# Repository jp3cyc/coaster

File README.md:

# coaster
光る！コースタです。いざって時(e.g. 友達が遊びに来た、地震、台風の時とか)にはArduinoとしても活躍します。

# 用意するもの
## 部品
- チップLED 1608サイズ 12個
- チップ抵抗 270Ω 1608サイズ 12個
- チップ抵抗 10kΩ 1608サイズ 1個
- ATMEGA328P-AU 1個
- 基板実装型スイッチ 1個
- CR2032表面実装型ケース 1個
- CR2032 1個

## 道具
- AVR書き込み機　または Arduino UNO
- はんだごて
- はんだ
- リフロー炉（あれば楽）
- クリームはんだ（あれば楽）
- ピンセット（あれば便利）
- 顕微鏡（あれば便利）
- レーザ加工機（自宅にあると◎、ない場合はファボラボ or カインズに行く、カッターで頑張るのもあり）

# How to makke
1. プリント基板を注文する。Fusion PCB、PCBgogo、Elecrowとか。10枚$10＋送料です。coaster/circuit/garb/coaster-garbdata.zipを送るだけ
1. プリント基板が届くまでに部品を注文する。http://aki.prioris.jp/list/31d5aa3b-d171-41f0-a121-0a985a356ac1/ ワンクリックですべての部品があきづきカートに入ります。一個分の部品です。
1. コースタ基板を入れるためのケースを作ります。coaster-cutting.aiに入っているデータを誤自宅のレーザカッタで切断します。データはIllustrator形式ですが、みるだけならCoral Drawとかでもいけます。
1. はんだづけします。
1. AVRのFuseビットを変更します。lfuse:0xe2, hfuse:0xde, efuse:0x07（書き込めない場合はY1に8MHzの水晶、C1,C2に22pFのコンデンサをつけてみる）(firwareフォルダにコマンドが入っています）
1. プログラムを書き込みます。coaster-firmware/coaster-firmware.ino.with_bootloader.eightanaloginputs.hexを書き込みます。
1. ボタン電池を入れて、スイッチを入れるとつくはずです。つかなければ、電池残量、スイッチ、はんだ付けを見てみます。

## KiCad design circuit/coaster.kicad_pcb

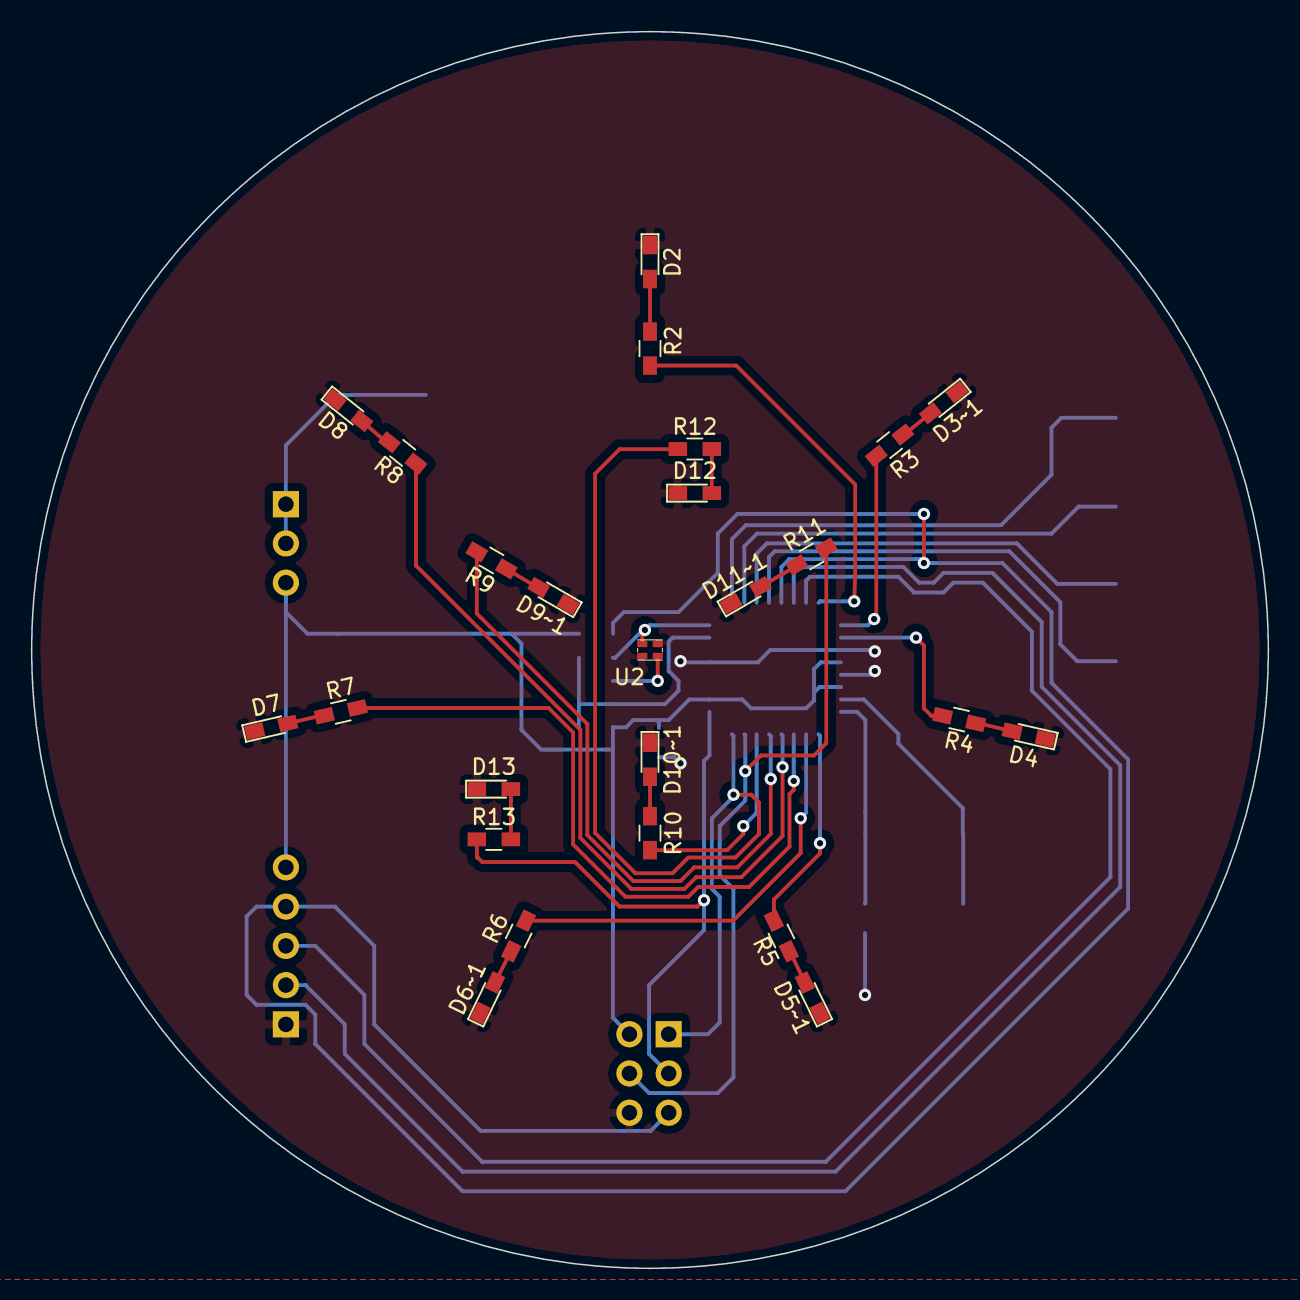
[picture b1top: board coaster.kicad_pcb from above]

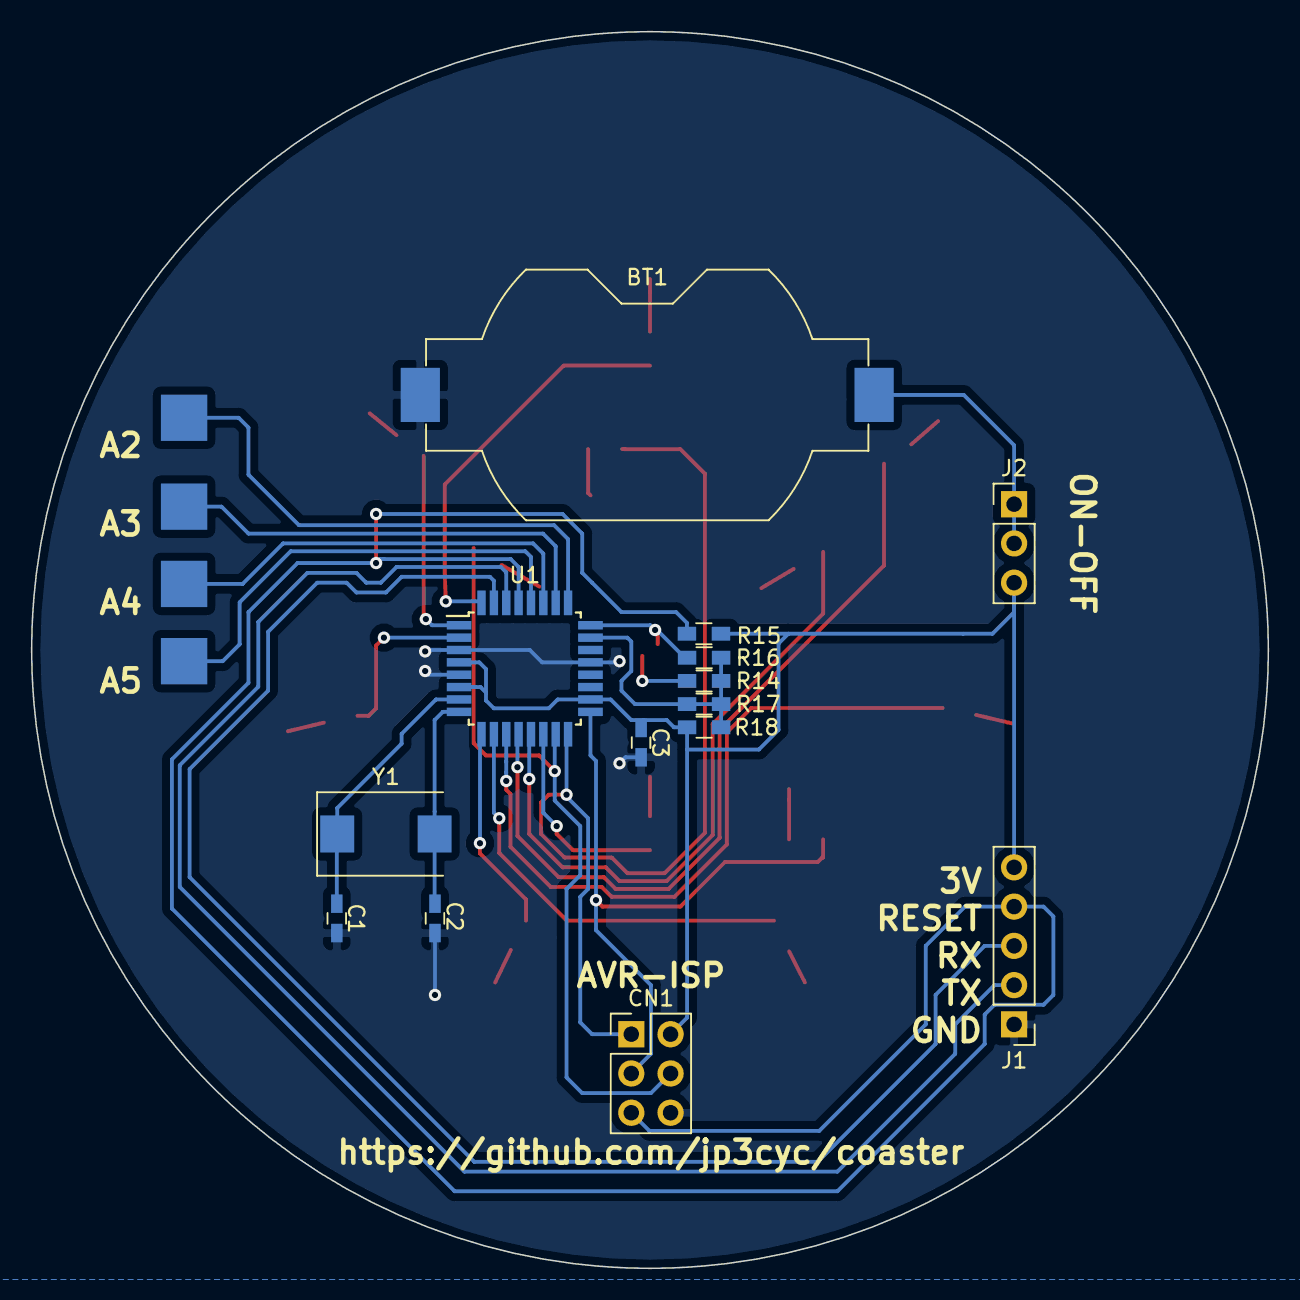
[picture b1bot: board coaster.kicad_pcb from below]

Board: 2 copper layers, 80.0 x 80.0 mm, 43 parts (18 on the bottom side), 39 nets.

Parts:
BT1: CR2032; Keystone_1058_1x2032-CoinCell
C1, C2: 22p; C_0603_HandSoldering
C3: 0.1u; C_0603_HandSoldering
CN1: AVR-ISP; Pin_Header_Straight_2x03_Pitch2.54mm
D2, D3~~1, D4, D5~~1, D6~~1, D7, D8, D9~~1, D10~~1, D11~~1, D12, D13: LED; LED_0603_HandSoldering
J1: Conn_01x05_Male; Pin_Header_Straight_1x05_Pitch2.54mm
J2: POWER SW; Pin_Header_Straight_1x03_Pitch2.54mm
J5: A2; Measurement_Point_Square-SMD-Pad_Big
J6: A3; Measurement_Point_Square-SMD-Pad_Big
J7: A4; Measurement_Point_Square-SMD-Pad_Big
J8: A5; Measurement_Point_Square-SMD-Pad_Big
R2, R3, R4, R5, R6, R7, R8, R9, R10, R11, R12, R13, R14, R16: 330; R_0603_HandSoldering
R15: 10k; R_0603_HandSoldering
R17, R18: 0; R_0603_HandSoldering
U1: ATmega328P-AU; TQFP-32_7x7mm_Pitch0.8mm
U2: SFH617A-1; NJK5901AR1
Y1: 8M; Crystal_SMD_EuroQuartz_MQ2-2pin_7.0x5.0mm

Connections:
+BATT: C3.1, CN1.2, J1.5, J2.3, R15.1, R18.1, U1.4, U1.6, U1.18
GND: BT1.2, C1.2, C2.2, C3.2, CN1.6, D2.1, D3~~1.1, D4.1, D5~~1.1, D6~~1.1, D7.1, D8.1, D9~~1.1, D10~~1.1, D11~~1.1, D12.1, D13.1, J1.1, U1.3, U1.5, U1.21, U2.2, U2.3
MISO: CN1.1, R12.1, U1.16
MOSI: CN1.4, R11.1, U1.15
unnamed: BT1.1, J2.1, J2.2
unnamed: C1.1, U1.7, Y1.1
unnamed: C2.1, U1.8, Y1.2
unnamed: D2.2, R2.2
unnamed: D3~~1.2, R3.2
unnamed: D4.2, R4.2
unnamed: D5~~1.2, R5.2
unnamed: D6~~1.2, R6.2
unnamed: D7.2, R7.2
unnamed: D8.2, R8.2
unnamed: D9~~1.2, R9.2
unnamed: D10~~1.2, R10.2
unnamed: D11~~1.2, R11.2
unnamed: D12.2, R12.2
unnamed: D13.2, R13.2
unnamed: J5.1, U1.25
unnamed: J6.1, U1.26
unnamed: J7.1, U1.27
unnamed: J8.1, U1.28
unnamed: R2.1, U1.32
unnamed: R3.1, U1.1
unnamed: R4.1, U1.2
unnamed: R5.1, U1.9
unnamed: R6.1, U1.10
unnamed: R7.1, U1.11
unnamed: R8.1, U1.12
unnamed: R9.1, U1.13
unnamed: R10.1, U1.14
unnamed: R14.1, R16.1, R17.1, R17.2, R18.2, U1.23
unnamed: R14.2, U2.1
unnamed: R16.2, U1.24, U2.4
RX: J1.3, U1.31
SCK: CN1.3, R13.1, U1.17
TX: J1.2, U1.30
~RESET: CN1.5, J1.4, R15.2, U1.29

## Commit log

2019-02-20 LICENSE
2019-03-19 initcommit うごいた
2019-03-19 Fix AVRマイコンの型番
